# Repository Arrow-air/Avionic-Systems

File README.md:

# Avionic-Systems
Avionic Systems Docs and Design Files for Arrow Aircraft

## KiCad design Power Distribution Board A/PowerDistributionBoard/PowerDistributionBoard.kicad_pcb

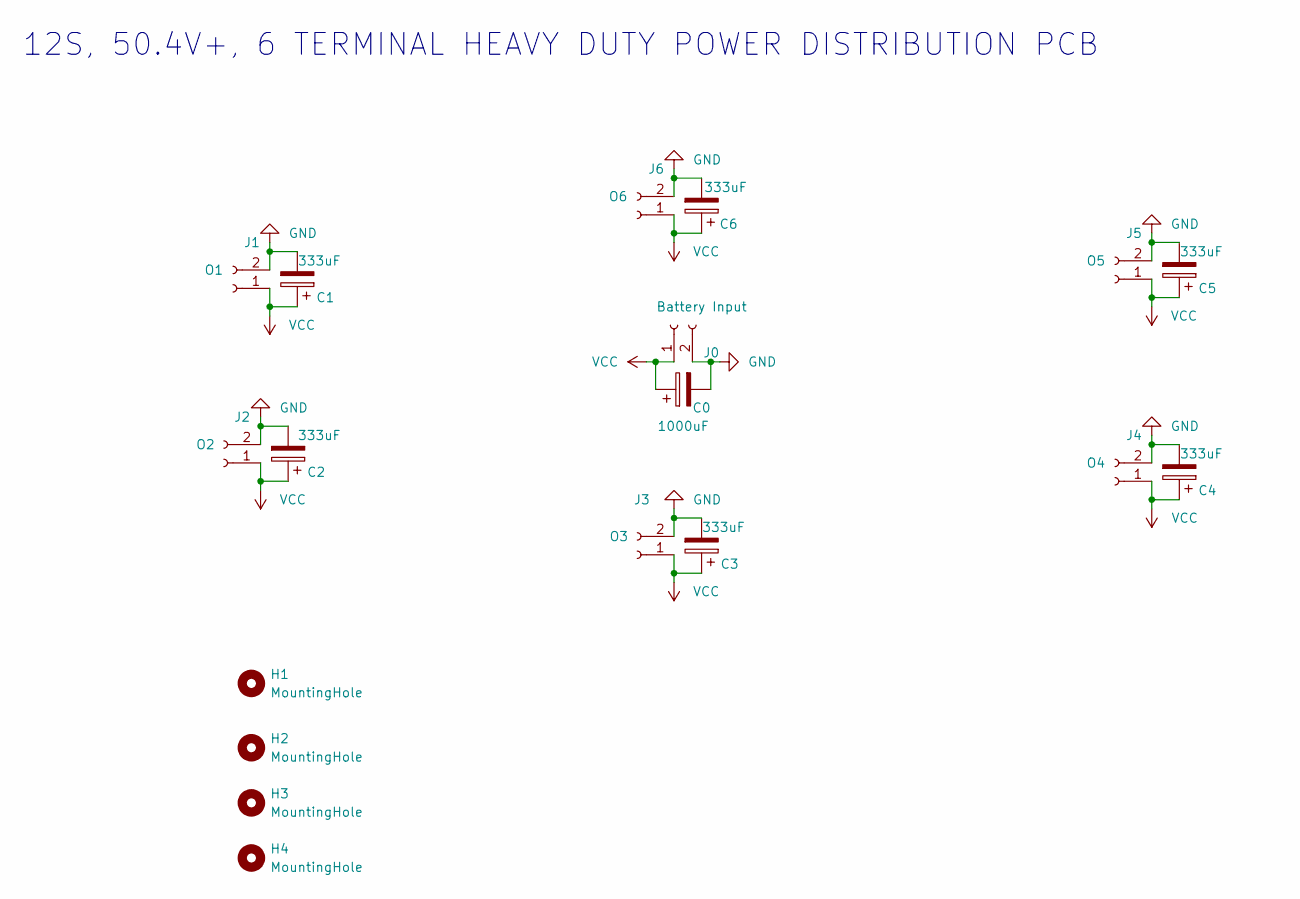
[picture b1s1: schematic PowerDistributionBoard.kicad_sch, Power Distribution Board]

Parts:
C0: 1000uF; CP_Radial_D10.0mm_P3.80mm
C1, C2, C3, C4, C5, C6: 333uF; CP_Radial_D10.0mm_P3.80mm
H1, H2, H3, H4: MountingHole; MountingHole_3.2mm_M3
J0: Battery Input; Banana_Jack_2Pin
J1: O1; AMASS_XT60-M_1x02_P7.20mm_Vertical
J2: O2; AMASS_XT60-M_1x02_P7.20mm_Vertical
J3: O3; AMASS_XT60-M_1x02_P7.20mm_Vertical
J4: O4; AMASS_XT60-M_1x02_P7.20mm_Vertical
J5: O5; AMASS_XT60-M_1x02_P7.20mm_Vertical
J6: O6; AMASS_XT60-M_1x02_P7.20mm_Vertical

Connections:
GND: C0.2, C1.2, C2.2, C3.2, C4.2, C5.2, C6.2, J0.2, J1.2, J2.2, J3.2, J4.2, J5.2, J6.2
VCC: C0.1, C1.1, C2.1, C3.1, C4.1, C5.1, C6.1, J0.1, J1.1, J2.1, J3.1, J4.1, J5.1, J6.1

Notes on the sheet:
12S, 50.4V+, 6 TERMINAL HEAVY DUTY POWER DISTRIBUTION PCB

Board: 2 copper layers, 18 parts (0 on the bottom side), 2 nets, no tracks yet.

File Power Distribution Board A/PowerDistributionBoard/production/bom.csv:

Designator,Footprint,Quantity,Value,LCSC Part #
C0,CP_Radial_D10.0mm_P3.80mm,1,470uF,"

C160628"
"C1, C2, C3, C4, C5, C6",CP_Radial_D10.0mm_P3.80mm,6,333uF,"
C233101"
"H1, H2, H3, H4",MountingHole_3.2mm_M3,4,MountingHole,
J0,Banana_Jack_2Pin,1,Battery Input,
J1,AMASS_XT60-M_1x02_P7.20mm_Vertical,1,O1,C98733
J2,AMASS_XT60-M_1x02_P7.20mm_Vertical,1,O2,C98733
J3,AMASS_XT60-M_1x02_P7.20mm_Vertical,1,O3,C98733 
J4,AMASS_XT60-M_1x02_P7.20mm_Vertical,1,O4,C98733
J5,AMASS_XT60-M_1x02_P7.20mm_Vertical,1,O5,C98733
J6,AMASS_XT60-M_1x02_P7.20mm_Vertical,1,O6,C98733

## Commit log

2022-11-30 Power Distribution Board V1
    Beefy beefy no frills PDB for Spearhead
2022-12-06 General Update
    Board Size Reduced
    Colour Scheme Update
2022-12-07 update
    photos
2022-12-09 Update
    Mounting Provisions Added
2023-12-06 CANBed Telemetry and BMS Code
    06/12/23 AD
    CANBed Telemetry
    BMS Contactor Code
    APD ESC Telemetry USB GUI
2023-12-06 Telemetry GUI Functional
    AD 06/12/23:
    Telemetry GUI Functional
    Voltage
    Current
    RPM
    Throttle
2023-12-06 update delay on precharge
2023-12-06 file name chnages
2023-12-06 update canID check
2023-12-20 Keep contactor closed
2023-12-20 Force contactorTrigger HIGH
2023-12-20 MCP CAN
2024-01-09 JoystickToPPM
    Test Script to Read USB Joysticks and Send the Data to Flight Controller as PPM signal
2024-01-28 Motor Test System Added
2024-04-26 Name Changes, PT3 Companion PC module creation
2024-04-30 getting going
2024-05-01 updates and re arranging
2024-05-12 updates
    UI some more ui element working
2024-05-17 Whole buncha updates and tests
2024-05-19 update with fixes for linux
2024-05-24 main
2024-05-30 moved companion PC to own repo
